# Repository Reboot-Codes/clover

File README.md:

<div align="center">

# C.L.O.V.E.R.

### Cybernetic Living Organism Variable Extension Regulator; Smart fursuit parts made for daily wear to help out your species dysphoria.

**Please note:** Clover is Currently NOT suitible for any sort of regular use and is being developed in sparse sprints as we can find time to do so.

</div>

---

## Features

- **Ease of Setup:** C.L.O.V.E.R.'s management software includes step by step guides on building, setup, and maintenence.
- **Focus on Security:** Every event and module is verified and authenticated with an explicit trust and permission framework *by the user*.
- **Open Extensibility:** C.L.O.V.E.R. ships with FLOSS APIs and an application management system which promotes open source projects.
- **Use Case Adaptability:** While originally designed for use in Smart Fursuits, C.L.O.V.E.R. can also be used for Cosplay and Body Modifications (e.g. Cyborgs).

## Usage

The currently planned workflow is to:

1. install a management application on an external device (like a PC, Laptop, Smartphone, or Tablet)
2. use it to plan out required materials, 
3. connect them, 
4. and flash them to create a working instance of C.L.O.V.E.R. 

Due to OS limitations, a linux/darwin desktop or a powerful android device is required for building C.L.O.V.E.R. firmwares. Otherwise, anything that supports the communication protocols configured in your instance and that has an application which speaks the management API can be used for external management/control once authenticated.

We also plan to make pre-built binaries available through a Nix cache to cut down on build times for CloverHub, C.O.R.E. components, and some supported configurations; but offline builds will always be an option.

## License, Disclaimer, and Other Legal Preface

C.L.O.V.E.R.'s primary orchestration process(es, a.k.a. CloverHub), reference API implementations (Tesseract, CarbonSteel, CarbonFiber), management software (Spanner), hardware (C.O.R.E.), and documentation are licensed under the GNU Affero General Public License version 3. CloverHub ships with or will download a copy of the repository it was built from to run C.O.R.E. and ensure AGPL compliance.

Software developed with any reference API implementations (Tesseract, CarbonSteel) may be covered under the AGPL as well. ***This is not legal advice***, but a notice to developers who may be considering building for C.L.O.V.E.R., that you may be required to publish your source code in accordance with the AGPL if you choose to make your software publicly accessable at all.

Of course, any contributor to this repository and associated materials does not provide any guarantee of any kind, nor will take liability for actions caused by or relating to C.L.O.V.E.R.

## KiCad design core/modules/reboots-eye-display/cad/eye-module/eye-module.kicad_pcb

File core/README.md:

# CORE

### C.L.O.V.E.R.'s Organizational Robotic Extremities; The offically maintained modules, applications, and expression packs for C.L.O.V.E.R.

[Check the docs for more info.](https://clover.reboot-codes.com/docs/core/intro)

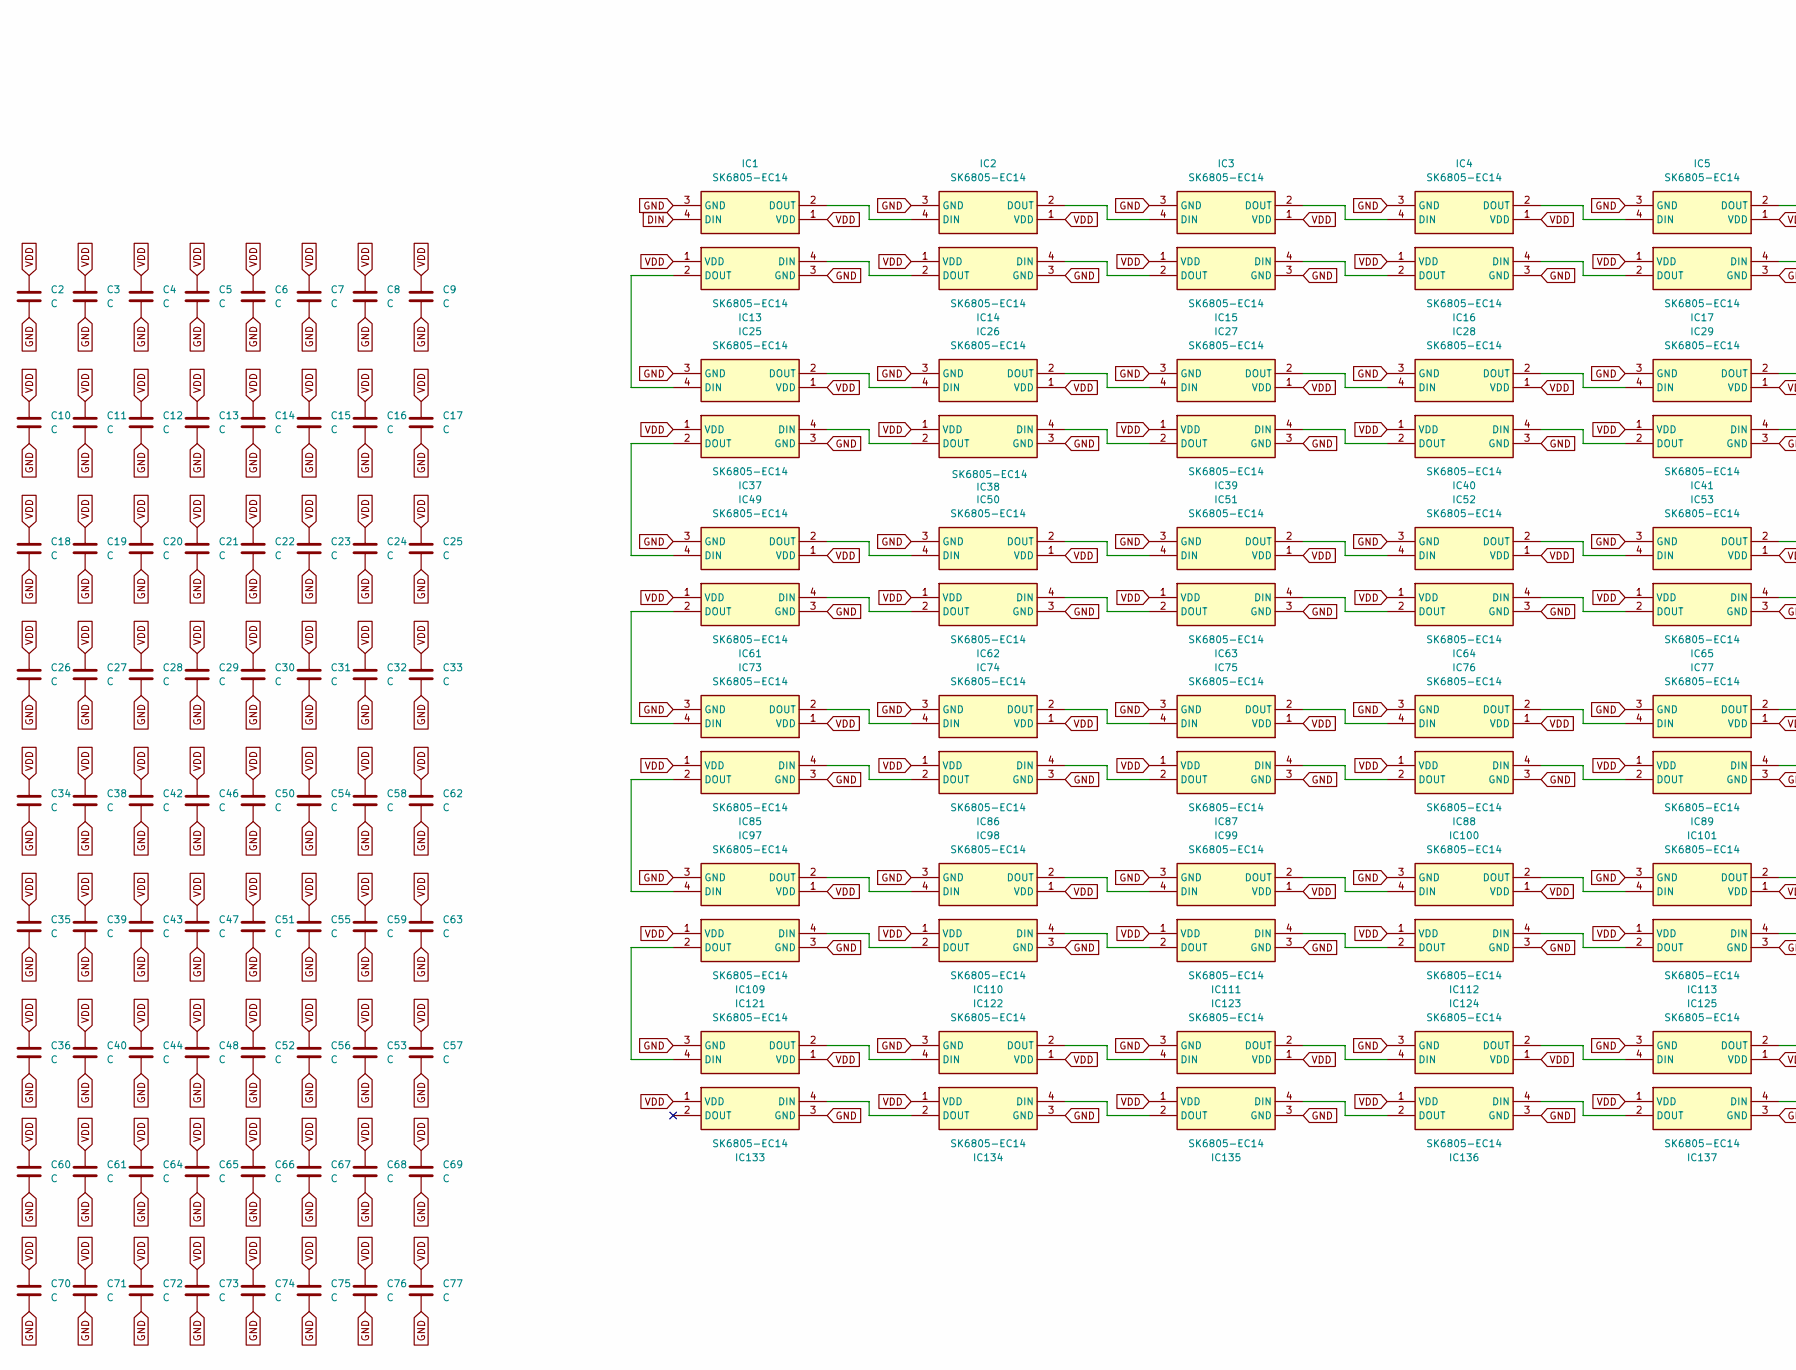
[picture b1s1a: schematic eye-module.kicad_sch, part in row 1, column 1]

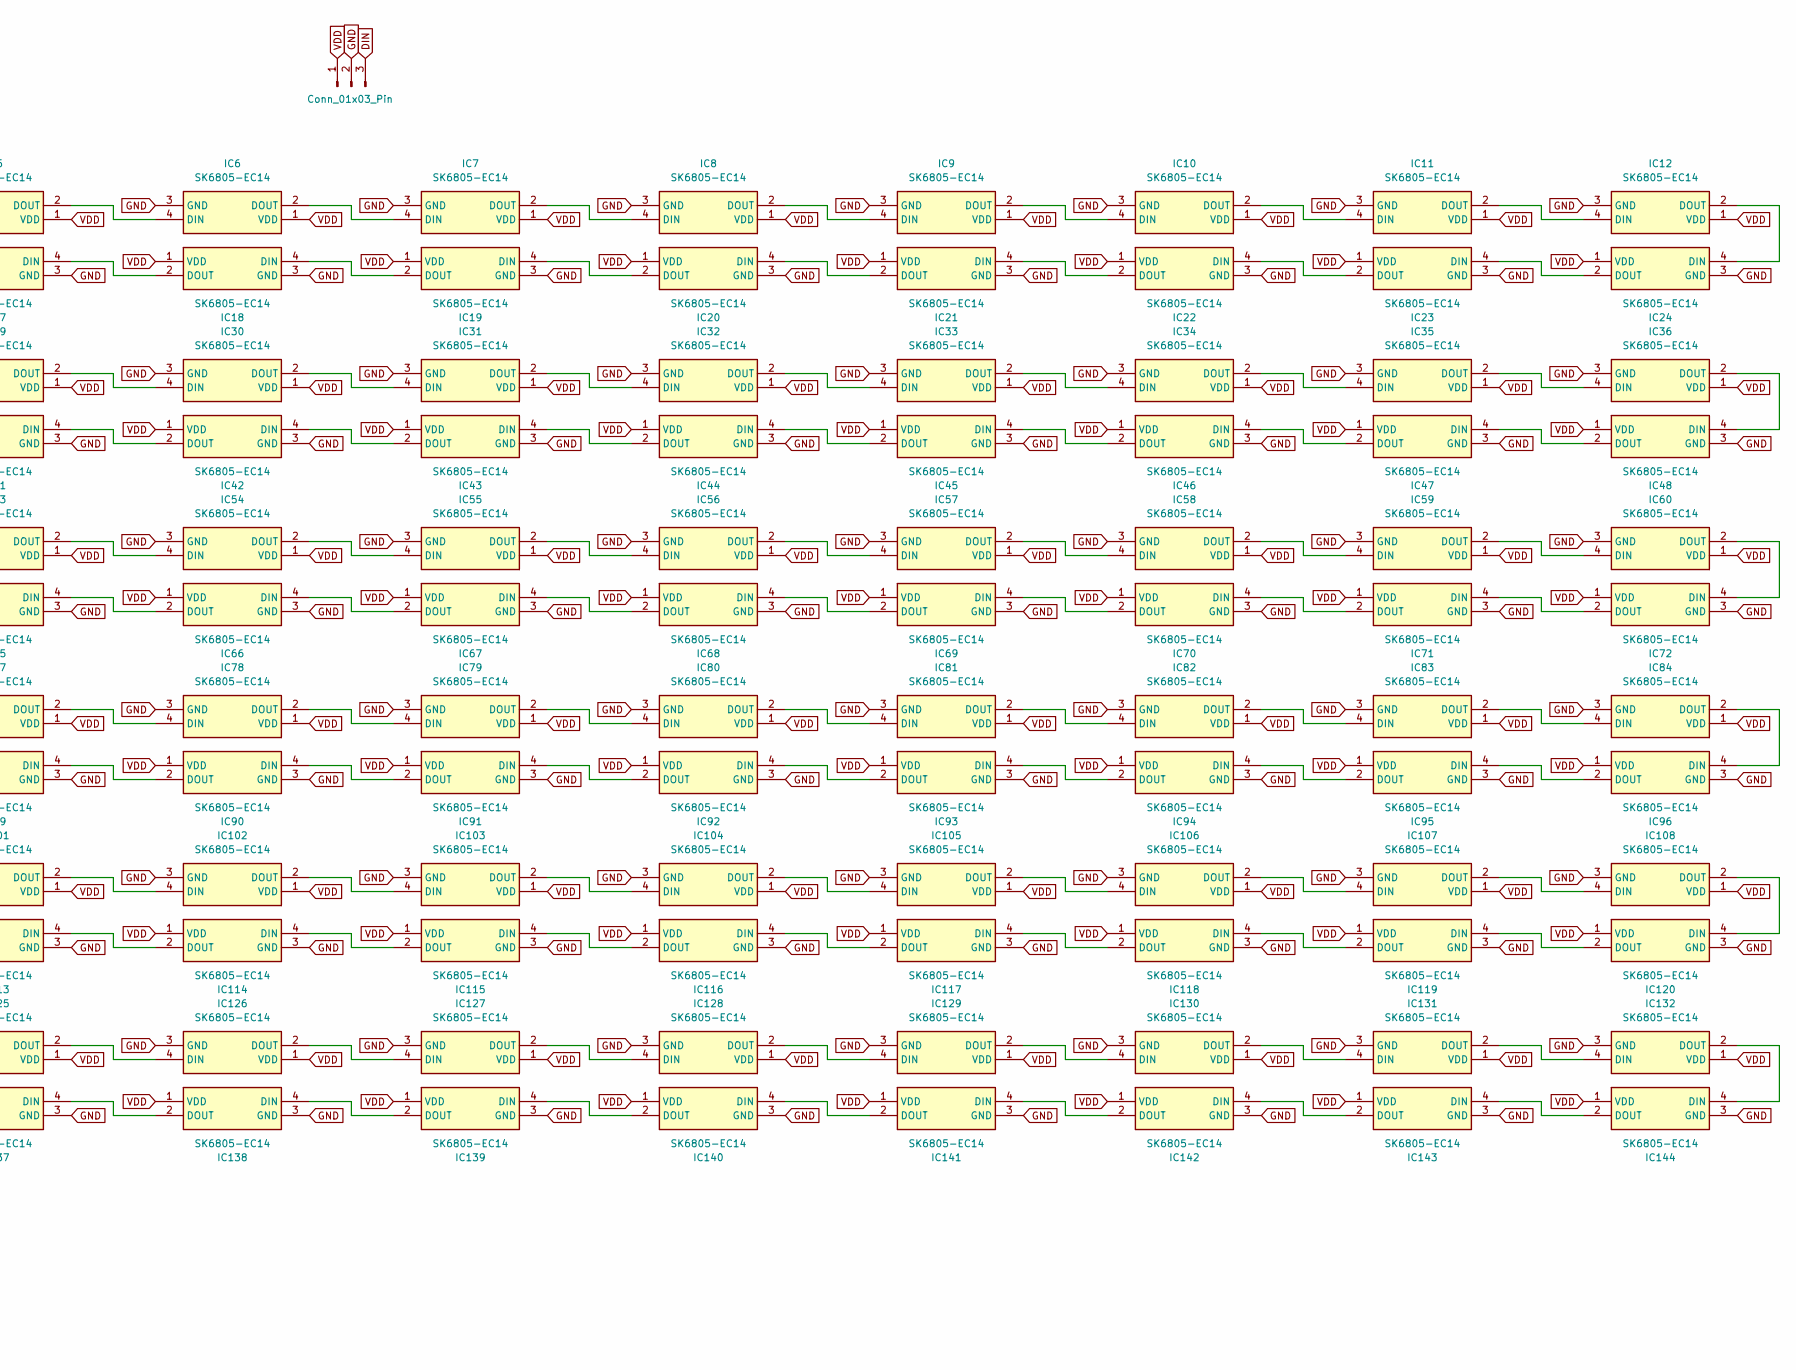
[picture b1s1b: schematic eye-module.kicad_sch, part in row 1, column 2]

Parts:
C2, C3, C4, C5, C6, C7, C8, C9, C10, C11, C12, C13, C14, C15, C16, C17, C18, C19, C20, C21, C22, C23, C24, C25, C26, C27, C28, C29, C30, C31, C32, C33, C34, C35, C36, C38, C39, C40, C42, C43, C44, C46, C47, C48, C50, C51, C52, C53, C54, C55, C56, C57, C58, C59, C60, C61, C62, C63, C64, C65, C66, C67, C68, C69, C70, C71, C72, C73, C74, C75, C76, C77: C; C_0603_1608Metric
IC1, IC2, IC3, IC4, IC5, IC6, IC7, IC8, IC9, IC10, IC11, IC12, IC13, IC14, IC15, IC16, IC17, IC18, IC19, IC20, IC21, IC22, IC23, IC24, IC25, IC26, IC27, IC28, IC29, IC30, IC31, IC32, IC33, IC34, IC35, IC36, IC37, IC38, IC39, IC40, IC41, IC42, IC43, IC44, IC45, IC46, IC47, IC48, IC49, IC50, IC51, IC52, IC53, IC54, IC55, IC56, IC57, IC58, IC59, IC60, IC61, IC62, IC63, IC64, IC65, IC66, IC67, IC68, IC69, IC70, IC71, IC72, IC73, IC74, IC75, IC76, IC77, IC78, IC79, IC80, IC81, IC82, IC83, IC84, IC85, IC86, IC87, IC88, IC89, IC90, IC91, IC92, IC93, IC94, IC95, IC96, IC97, IC98, IC99, IC100, IC101, IC102, IC103, IC104, IC105, IC106, IC107, IC108, IC109, IC110, IC111, IC112, IC113, IC114, IC115, IC116, IC117, IC118, IC119, IC120, IC121, IC122, IC123, IC124, IC125, IC126, IC127, IC128, IC129, IC130, IC131, IC132, IC133, IC134, IC135, IC136, IC137, IC138, IC139, IC140, IC141, IC142, IC143, IC144: SK6805-EC14; LED_SK6805_EC14; Manufacturer_Part_Number sk6805-ec14
J1: Conn_01x03_Pin; PinHeader_1x03_P1.00mm_Horizontal

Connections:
DIN: IC1.4 (DIN), J1.3
GND: C2.2, C3.2, C4.2, C5.2, C6.2, C7.2, C8.2, C9.2, C10.2, C11.2, C12.2, C13.2, C14.2, C15.2, C16.2, C17.2, C18.2, C19.2, C20.2, C21.2, C22.2, C23.2, C24.2, C25.2, C26.2, C27.2, C28.2, C29.2, C30.2, C31.2, C32.2, C33.2, C34.2, C35.2, C36.2, C38.2, C39.2, C40.2, C42.2, C43.2, C44.2, C46.2, C47.2, C48.2, C50.2, C51.2, C52.2, C53.2, C54.2, C55.2, C56.2, C57.2, C58.2, C59.2, C60.2, C61.2, C62.2, C63.2, C64.2, C65.2, C66.2, C67.2, C68.2, C69.2, C70.2, C71.2, C72.2, C73.2, C74.2, C75.2, C76.2, C77.2, IC1.3 (GND), IC2.3 (GND), IC3.3 (GND), IC4.3 (GND), IC5.3 (GND), IC6.3 (GND), IC7.3 (GND), IC8.3 (GND), IC9.3 (GND), IC10.3 (GND), IC11.3 (GND), IC12.3 (GND), IC13.3 (GND), IC14.3 (GND), IC15.3 (GND), IC16.3 (GND), IC17.3 (GND), IC18.3 (GND), IC19.3 (GND), IC20.3 (GND), IC21.3 (GND), IC22.3 (GND), IC23.3 (GND), IC24.3 (GND), IC25.3 (GND), IC26.3 (GND), IC27.3 (GND), IC28.3 (GND), IC29.3 (GND), IC30.3 (GND), IC31.3 (GND), IC32.3 (GND), IC33.3 (GND), IC34.3 (GND), IC35.3 (GND), IC36.3 (GND), IC37.3 (GND), IC38.3 (GND), IC39.3 (GND), IC40.3 (GND), IC41.3 (GND), IC42.3 (GND), IC43.3 (GND), IC44.3 (GND), IC45.3 (GND), IC46.3 (GND), IC47.3 (GND), IC48.3 (GND), IC49.3 (GND), IC50.3 (GND), IC51.3 (GND), IC52.3 (GND), IC53.3 (GND), IC54.3 (GND), IC55.3 (GND), IC56.3 (GND), IC57.3 (GND), IC58.3 (GND), IC59.3 (GND), IC60.3 (GND), IC61.3 (GND), IC62.3 (GND), IC63.3 (GND), IC64.3 (GND), IC65.3 (GND), IC66.3 (GND), IC67.3 (GND), IC68.3 (GND), IC69.3 (GND), IC70.3 (GND), IC71.3 (GND), IC72.3 (GND), IC73.3 (GND), IC74.3 (GND), IC75.3 (GND), IC76.3 (GND), IC77.3 (GND), IC78.3 (GND), IC79.3 (GND), IC80.3 (GND), IC81.3 (GND), IC82.3 (GND), IC83.3 (GND), IC84.3 (GND), IC85.3 (GND), IC86.3 (GND), IC87.3 (GND), IC88.3 (GND), IC89.3 (GND), IC90.3 (GND), IC91.3 (GND), IC92.3 (GND), IC93.3 (GND), IC94.3 (GND), IC95.3 (GND), IC96.3 (GND), IC97.3 (GND), IC98.3 (GND), IC99.3 (GND), IC100.3 (GND), IC101.3 (GND), IC102.3 (GND), IC103.3 (GND), IC104.3 (GND), IC105.3 (GND), IC106.3 (GND), IC107.3 (GND), IC108.3 (GND), IC109.3 (GND), IC110.3 (GND), IC111.3 (GND), IC112.3 (GND), IC113.3 (GND), IC114.3 (GND), IC115.3 (GND), IC116.3 (GND), IC117.3 (GND), IC118.3 (GND), IC119.3 (GND), IC120.3 (GND), IC121.3 (GND), IC122.3 (GND), IC123.3 (GND), IC124.3 (GND), IC125.3 (GND), IC126.3 (GND), IC127.3 (GND), IC128.3 (GND), IC129.3 (GND), IC130.3 (GND), IC131.3 (GND), IC132.3 (GND), IC133.3 (GND), IC134.3 (GND), IC135.3 (GND), IC136.3 (GND), IC137.3 (GND), IC138.3 (GND), IC139.3 (GND), IC140.3 (GND), IC141.3 (GND), IC142.3 (GND), IC143.3 (GND), IC144.3 (GND), J1.2
unnamed: IC1.2 (DOUT), IC2.4 (DIN)
unnamed: IC2.2 (DOUT), IC3.4 (DIN)
unnamed: IC3.2 (DOUT), IC4.4 (DIN)
unnamed: IC4.2 (DOUT), IC5.4 (DIN)
unnamed: IC5.2 (DOUT), IC6.4 (DIN)
unnamed: IC6.2 (DOUT), IC7.4 (DIN)
unnamed: IC7.2 (DOUT), IC8.4 (DIN)
unnamed: IC8.2 (DOUT), IC9.4 (DIN)
unnamed: IC9.2 (DOUT), IC10.4 (DIN)
unnamed: IC10.2 (DOUT), IC11.4 (DIN)
unnamed: IC11.2 (DOUT), IC12.4 (DIN)
unnamed: IC12.2 (DOUT), IC24.4 (DIN)
unnamed: IC13.4 (DIN), IC14.2 (DOUT)
unnamed: IC13.2 (DOUT), IC25.4 (DIN)
unnamed: IC14.4 (DIN), IC15.2 (DOUT)
unnamed: IC15.4 (DIN), IC16.2 (DOUT)
unnamed: IC16.4 (DIN), IC17.2 (DOUT)
unnamed: IC17.4 (DIN), IC18.2 (DOUT)
unnamed: IC18.4 (DIN), IC19.2 (DOUT)
unnamed: IC19.4 (DIN), IC20.2 (DOUT)
unnamed: IC20.4 (DIN), IC21.2 (DOUT)
unnamed: IC21.4 (DIN), IC22.2 (DOUT)
unnamed: IC22.4 (DIN), IC23.2 (DOUT)
unnamed: IC23.4 (DIN), IC24.2 (DOUT)
unnamed: IC25.2 (DOUT), IC26.4 (DIN)
unnamed: IC26.2 (DOUT), IC27.4 (DIN)
unnamed: IC27.2 (DOUT), IC28.4 (DIN)
unnamed: IC28.2 (DOUT), IC29.4 (DIN)
unnamed: IC29.2 (DOUT), IC30.4 (DIN)
unnamed: IC30.2 (DOUT), IC31.4 (DIN)
unnamed: IC31.2 (DOUT), IC32.4 (DIN)
unnamed: IC32.2 (DOUT), IC33.4 (DIN)
unnamed: IC33.2 (DOUT), IC34.4 (DIN)
unnamed: IC34.2 (DOUT), IC35.4 (DIN)
unnamed: IC35.2 (DOUT), IC36.4 (DIN)
unnamed: IC36.2 (DOUT), IC48.4 (DIN)
unnamed: IC37.4 (DIN), IC38.2 (DOUT)
unnamed: IC37.2 (DOUT), IC49.4 (DIN)
unnamed: IC38.4 (DIN), IC39.2 (DOUT)
unnamed: IC39.4 (DIN), IC40.2 (DOUT)
unnamed: IC40.4 (DIN), IC41.2 (DOUT)
unnamed: IC41.4 (DIN), IC42.2 (DOUT)
unnamed: IC42.4 (DIN), IC43.2 (DOUT)
unnamed: IC43.4 (DIN), IC44.2 (DOUT)
unnamed: IC44.4 (DIN), IC45.2 (DOUT)
unnamed: IC45.4 (DIN), IC46.2 (DOUT)
unnamed: IC46.4 (DIN), IC47.2 (DOUT)
unnamed: IC47.4 (DIN), IC48.2 (DOUT)
unnamed: IC49.2 (DOUT), IC50.4 (DIN)
unnamed: IC50.2 (DOUT), IC51.4 (DIN)
unnamed: IC51.2 (DOUT), IC52.4 (DIN)
unnamed: IC52.2 (DOUT), IC53.4 (DIN)
unnamed: IC53.2 (DOUT), IC54.4 (DIN)
unnamed: IC54.2 (DOUT), IC55.4 (DIN)
unnamed: IC55.2 (DOUT), IC56.4 (DIN)
unnamed: IC56.2 (DOUT), IC57.4 (DIN)
unnamed: IC57.2 (DOUT), IC58.4 (DIN)
unnamed: IC58.2 (DOUT), IC59.4 (DIN)
unnamed: IC59.2 (DOUT), IC60.4 (DIN)
unnamed: IC60.2 (DOUT), IC72.4 (DIN)
unnamed: IC61.4 (DIN), IC62.2 (DOUT)
unnamed: IC61.2 (DOUT), IC73.4 (DIN)
unnamed: IC62.4 (DIN), IC63.2 (DOUT)
unnamed: IC63.4 (DIN), IC64.2 (DOUT)
unnamed: IC64.4 (DIN), IC65.2 (DOUT)
unnamed: IC65.4 (DIN), IC66.2 (DOUT)
unnamed: IC66.4 (DIN), IC67.2 (DOUT)
unnamed: IC67.4 (DIN), IC68.2 (DOUT)
unnamed: IC68.4 (DIN), IC69.2 (DOUT)
unnamed: IC69.4 (DIN), IC70.2 (DOUT)
unnamed: IC70.4 (DIN), IC71.2 (DOUT)
unnamed: IC71.4 (DIN), IC72.2 (DOUT)
unnamed: IC73.2 (DOUT), IC74.4 (DIN)
unnamed: IC74.2 (DOUT), IC75.4 (DIN)
unnamed: IC75.2 (DOUT), IC76.4 (DIN)
unnamed: IC76.2 (DOUT), IC77.4 (DIN)
unnamed: IC77.2 (DOUT), IC78.4 (DIN)
unnamed: IC78.2 (DOUT), IC79.4 (DIN)
unnamed: IC79.2 (DOUT), IC80.4 (DIN)
unnamed: IC80.2 (DOUT), IC81.4 (DIN)
unnamed: IC81.2 (DOUT), IC82.4 (DIN)
unnamed: IC82.2 (DOUT), IC83.4 (DIN)
unnamed: IC83.2 (DOUT), IC84.4 (DIN)
unnamed: IC84.2 (DOUT), IC96.4 (DIN)
unnamed: IC85.4 (DIN), IC86.2 (DOUT)
unnamed: IC85.2 (DOUT), IC97.4 (DIN)
unnamed: IC86.4 (DIN), IC87.2 (DOUT)
unnamed: IC87.4 (DIN), IC88.2 (DOUT)
unnamed: IC88.4 (DIN), IC89.2 (DOUT)
unnamed: IC89.4 (DIN), IC90.2 (DOUT)
unnamed: IC90.4 (DIN), IC91.2 (DOUT)
unnamed: IC91.4 (DIN), IC92.2 (DOUT)
unnamed: IC92.4 (DIN), IC93.2 (DOUT)
unnamed: IC93.4 (DIN), IC94.2 (DOUT)
unnamed: IC94.4 (DIN), IC95.2 (DOUT)
unnamed: IC95.4 (DIN), IC96.2 (DOUT)
unnamed: IC97.2 (DOUT), IC98.4 (DIN)
unnamed: IC98.2 (DOUT), IC99.4 (DIN)
unnamed: IC99.2 (DOUT), IC100.4 (DIN)
unnamed: IC100.2 (DOUT), IC101.4 (DIN)
unnamed: IC101.2 (DOUT), IC102.4 (DIN)
unnamed: IC102.2 (DOUT), IC103.4 (DIN)
unnamed: IC103.2 (DOUT), IC104.4 (DIN)
unnamed: IC104.2 (DOUT), IC105.4 (DIN)
unnamed: IC105.2 (DOUT), IC106.4 (DIN)
unnamed: IC106.2 (DOUT), IC107.4 (DIN)
unnamed: IC107.2 (DOUT), IC108.4 (DIN)
unnamed: IC108.2 (DOUT), IC120.4 (DIN)
unnamed: IC109.4 (DIN), IC110.2 (DOUT)
unnamed: IC109.2 (DOUT), IC121.4 (DIN)
unnamed: IC110.4 (DIN), IC111.2 (DOUT)
unnamed: IC111.4 (DIN), IC112.2 (DOUT)
unnamed: IC112.4 (DIN), IC113.2 (DOUT)
unnamed: IC113.4 (DIN), IC114.2 (DOUT)
unnamed: IC114.4 (DIN), IC115.2 (DOUT)
unnamed: IC115.4 (DIN), IC116.2 (DOUT)
unnamed: IC116.4 (DIN), IC117.2 (DOUT)
unnamed: IC117.4 (DIN), IC118.2 (DOUT)
unnamed: IC118.4 (DIN), IC119.2 (DOUT)
unnamed: IC119.4 (DIN), IC120.2 (DOUT)
unnamed: IC121.2 (DOUT), IC122.4 (DIN)
unnamed: IC122.2 (DOUT), IC123.4 (DIN)
unnamed: IC123.2 (DOUT), IC124.4 (DIN)
unnamed: IC124.2 (DOUT), IC125.4 (DIN)
unnamed: IC125.2 (DOUT), IC126.4 (DIN)
unnamed: IC126.2 (DOUT), IC127.4 (DIN)
unnamed: IC127.2 (DOUT), IC128.4 (DIN)
unnamed: IC128.2 (DOUT), IC129.4 (DIN)
unnamed: IC129.2 (DOUT), IC130.4 (DIN)
unnamed: IC130.2 (DOUT), IC131.4 (DIN)
unnamed: IC131.2 (DOUT), IC132.4 (DIN)
unnamed: IC132.2 (DOUT), IC144.4 (DIN)
unnamed: IC133.4 (DIN), IC134.2 (DOUT)
unnamed: IC134.4 (DIN), IC135.2 (DOUT)
unnamed: IC135.4 (DIN), IC136.2 (DOUT)
unnamed: IC136.4 (DIN), IC137.2 (DOUT)
unnamed: IC137.4 (DIN), IC138.2 (DOUT)
unnamed: IC138.4 (DIN), IC139.2 (DOUT)
unnamed: IC139.4 (DIN), IC140.2 (DOUT)
unnamed: IC140.4 (DIN), IC141.2 (DOUT)
unnamed: IC141.4 (DIN), IC142.2 (DOUT)
unnamed: IC142.4 (DIN), IC143.2 (DOUT)
unnamed: IC143.4 (DIN), IC144.2 (DOUT)
VDD: C2.1, C3.1, C4.1, C5.1, C6.1, C7.1, C8.1, C9.1, C10.1, C11.1, C12.1, C13.1, C14.1, C15.1, C16.1, C17.1, C18.1, C19.1, C20.1, C21.1, C22.1, C23.1, C24.1, C25.1, C26.1, C27.1, C28.1, C29.1, C30.1, C31.1, C32.1, C33.1, C34.1, C35.1, C36.1, C38.1, C39.1, C40.1, C42.1, C43.1, C44.1, C46.1, C47.1, C48.1, C50.1, C51.1, C52.1, C53.1, C54.1, C55.1, C56.1, C57.1, C58.1, C59.1, C60.1, C61.1, C62.1, C63.1, C64.1, C65.1, C66.1, C67.1, C68.1, C69.1, C70.1, C71.1, C72.1, C73.1, C74.1, C75.1, C76.1, C77.1, IC1.1 (VDD), IC2.1 (VDD), IC3.1 (VDD), IC4.1 (VDD), IC5.1 (VDD), IC6.1 (VDD), IC7.1 (VDD), IC8.1 (VDD), IC9.1 (VDD), IC10.1 (VDD), IC11.1 (VDD), IC12.1 (VDD), IC13.1 (VDD), IC14.1 (VDD), IC15.1 (VDD), IC16.1 (VDD), IC17.1 (VDD), IC18.1 (VDD), IC19.1 (VDD), IC20.1 (VDD), IC21.1 (VDD), IC22.1 (VDD), IC23.1 (VDD), IC24.1 (VDD), IC25.1 (VDD), IC26.1 (VDD), IC27.1 (VDD), IC28.1 (VDD), IC29.1 (VDD), IC30.1 (VDD), IC31.1 (VDD), IC32.1 (VDD), IC33.1 (VDD), IC34.1 (VDD), IC35.1 (VDD), IC36.1 (VDD), IC37.1 (VDD), IC38.1 (VDD), IC39.1 (VDD), IC40.1 (VDD), IC41.1 (VDD), IC42.1 (VDD), IC43.1 (VDD), IC44.1 (VDD), IC45.1 (VDD), IC46.1 (VDD), IC47.1 (VDD), IC48.1 (VDD), IC49.1 (VDD), IC50.1 (VDD), IC51.1 (VDD), IC52.1 (VDD), IC53.1 (VDD), IC54.1 (VDD), IC55.1 (VDD), IC56.1 (VDD), IC57.1 (VDD), IC58.1 (VDD), IC59.1 (VDD), IC60.1 (VDD), IC61.1 (VDD), IC62.1 (VDD), IC63.1 (VDD), IC64.1 (VDD), IC65.1 (VDD), IC66.1 (VDD), IC67.1 (VDD), IC68.1 (VDD), IC69.1 (VDD), IC70.1 (VDD), IC71.1 (VDD), IC72.1 (VDD), IC73.1 (VDD), IC74.1 (VDD), IC75.1 (VDD), IC76.1 (VDD), IC77.1 (VDD), IC78.1 (VDD), IC79.1 (VDD), IC80.1 (VDD), IC81.1 (VDD), IC82.1 (VDD), IC83.1 (VDD), IC84.1 (VDD), IC85.1 (VDD), IC86.1 (VDD), IC87.1 (VDD), IC88.1 (VDD), IC89.1 (VDD), IC90.1 (VDD), IC91.1 (VDD), IC92.1 (VDD), IC93.1 (VDD), IC94.1 (VDD), IC95.1 (VDD), IC96.1 (VDD), IC97.1 (VDD), IC98.1 (VDD), IC99.1 (VDD), IC100.1 (VDD), IC101.1 (VDD), IC102.1 (VDD), IC103.1 (VDD), IC104.1 (VDD), IC105.1 (VDD), IC106.1 (VDD), IC107.1 (VDD), IC108.1 (VDD), IC109.1 (VDD), IC110.1 (VDD), IC111.1 (VDD), IC112.1 (VDD), IC113.1 (VDD), IC114.1 (VDD), IC115.1 (VDD), IC116.1 (VDD), IC117.1 (VDD), IC118.1 (VDD), IC119.1 (VDD), IC120.1 (VDD), IC121.1 (VDD), IC122.1 (VDD), IC123.1 (VDD), IC124.1 (VDD), IC125.1 (VDD), IC126.1 (VDD), IC127.1 (VDD), IC128.1 (VDD), IC129.1 (VDD), IC130.1 (VDD), IC131.1 (VDD), IC132.1 (VDD), IC133.1 (VDD), IC134.1 (VDD), IC135.1 (VDD), IC136.1 (VDD), IC137.1 (VDD), IC138.1 (VDD), IC139.1 (VDD), IC140.1 (VDD), IC141.1 (VDD), IC142.1 (VDD), IC143.1 (VDD), IC144.1 (VDD), J1.1

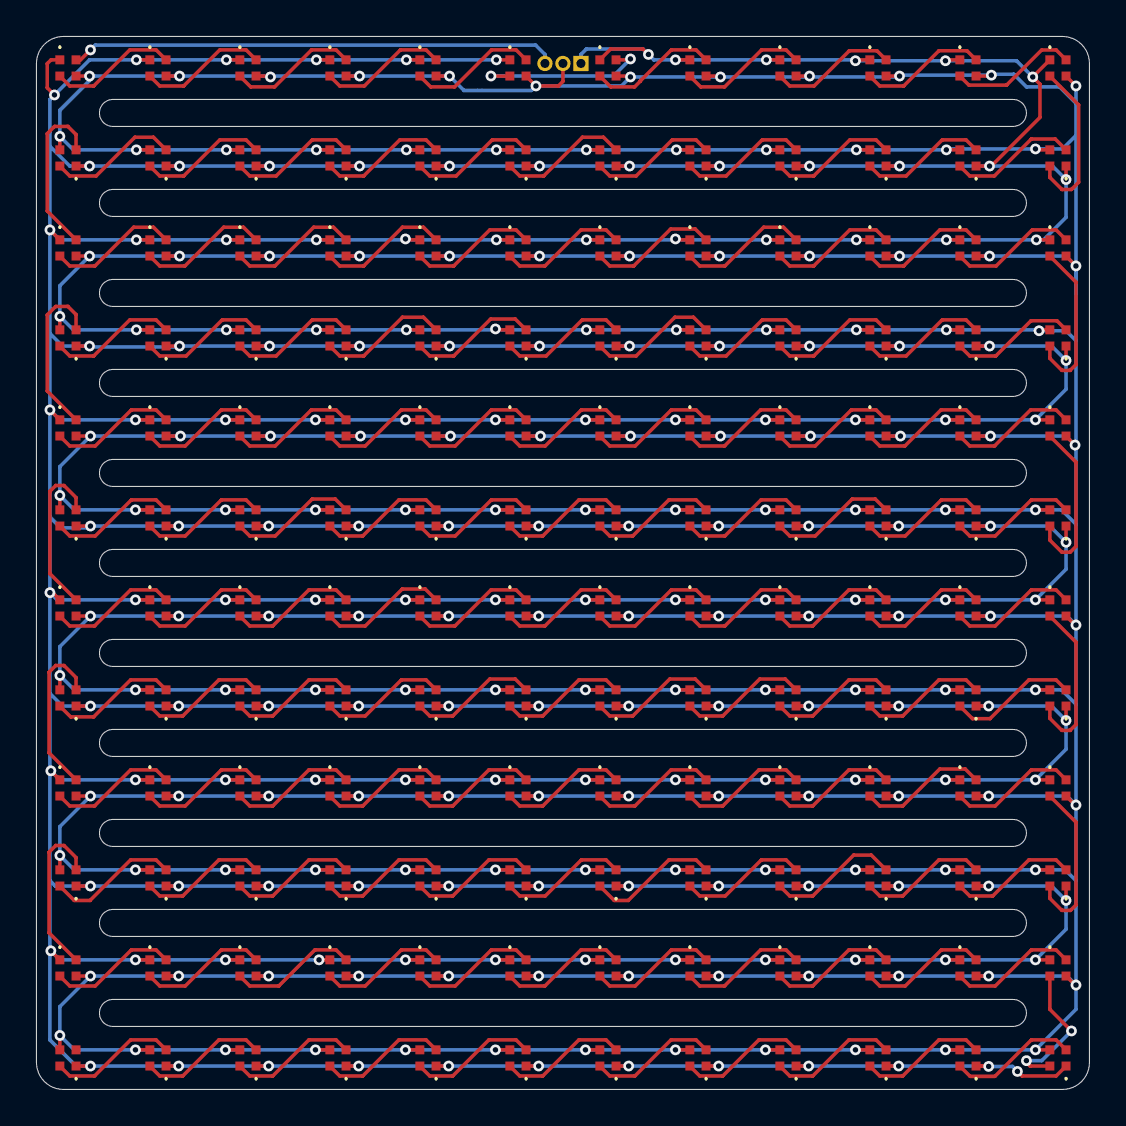
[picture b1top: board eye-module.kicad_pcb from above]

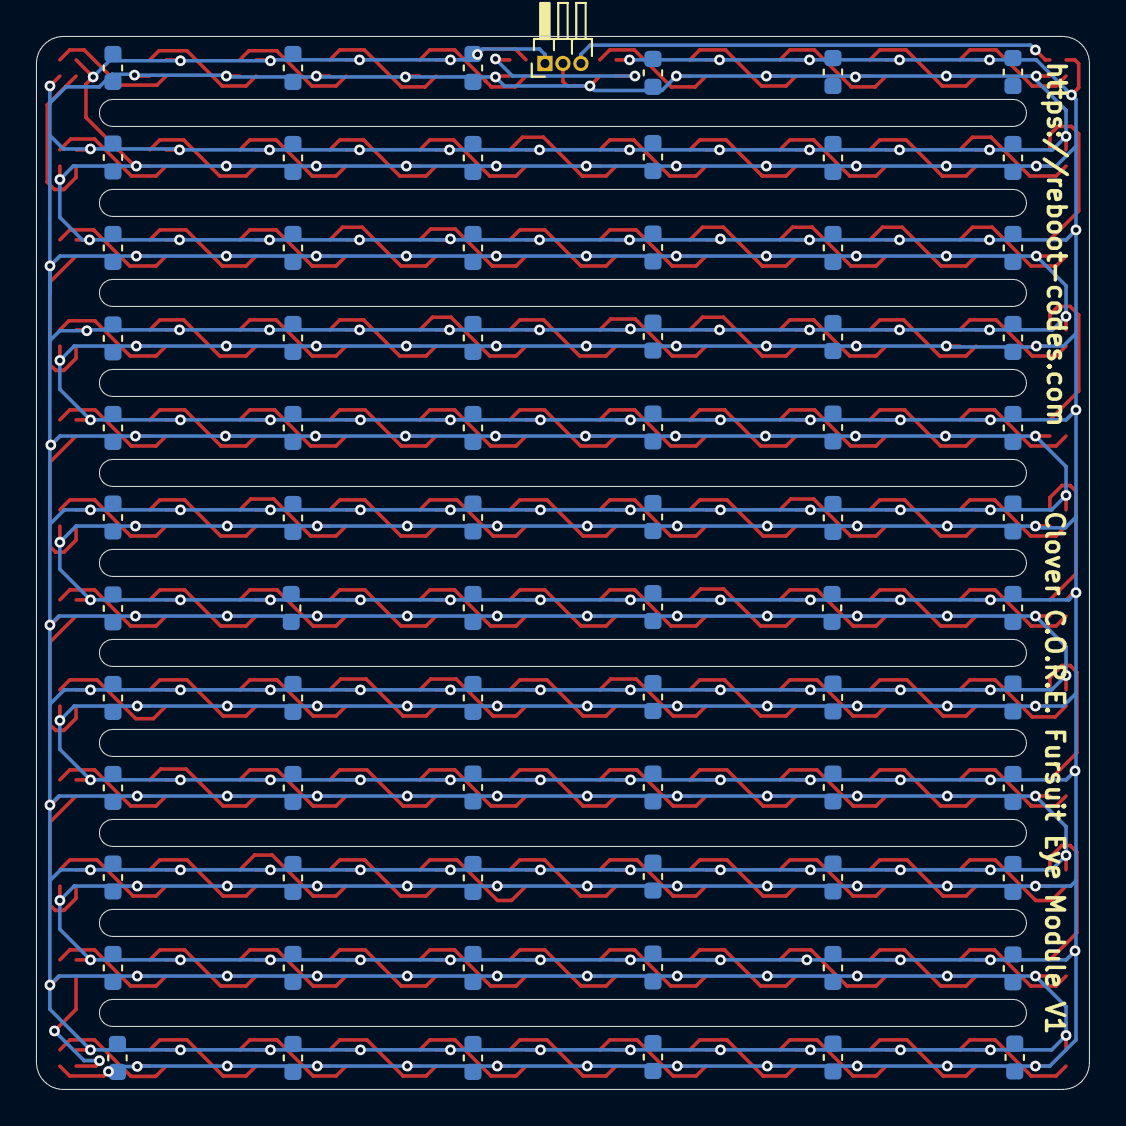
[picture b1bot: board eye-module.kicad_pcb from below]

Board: 2 copper layers, 58.5 x 58.5 mm, 217 parts (73 on the bottom side), 146 nets.

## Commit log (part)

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2024-08-06 Add message ids.
2024-08-06 Make sure to log the client that caused a WS error.
2024-08-06 Add docs website!
2024-08-06 Add the real readme...
2024-08-06 Add GH pages action.
2024-08-06 Fix node.js setup for GH Action.
2024-08-06 Shhhhhh~ I'm sure frozen lockfile doesn't matter for docs.
2024-08-06 Fix baseUrl and make sure docs builds only happen when docs are changed.
2024-08-07 Add `echo` option to API keys and add more docs.
2024-09-01 Reorganize server.
2024-09-01 Rename server to EVTBuzz
2024-09-01 Update docs to reflect new organization.
2024-09-01 Move to custom subdomain
2024-09-01 Fix broken docs links
2024-09-25 Add more IPC channels, add core user account generation.
2024-09-26 Complete IPC between core threads.
2024-09-26 Setup EvtBuzz's IPC dispatchers.
2024-09-27 Add Spanner to docs.
2024-09-27 Add deps on Taurus
2024-09-27 Refactor Models and Ensure Proper Formatting.
2024-09-27 Broken: Attempting SIGINT Handling, ModMan formation.
2024-09-28 Add stopping code. One module will always linger...?
2024-09-28 Fix SIGINT handling
2024-09-28 Add signal handling to all configs and add windows support.
2024-09-30 Move cargo config to root.
2024-09-30 Add spanner's template code and use cargo workspace.
2024-09-30 Restructure documentation.
2024-09-30 Fix broken links
2024-09-30 Clean up.
2024-09-30 Oops. Yeah, that's not the name of the executable anymore...
2024-09-30 Fix root domain
2024-10-01 Note to self: Move init hooks into cancelable closures.
2024-10-01 Remove the todo lol.
2024-10-01 Fix evtbuzz.
2024-10-02 Add more docs.
2024-10-03 Add more docs
2024-11-14 Add AppDaemon and Warehouse beginnings. Yeah, we need to stick to one thing at a time lmfao.
2024-11-14 Warehouse now manages configuration files properly.
2024-11-14 Add repository serialization
2024-11-14 Add libgit2 code to clone and update repos - todo: Create repo directory structure!
2024-11-15 Repo manifest resolution
2024-11-16 Module imports done... now for apps...
2024-11-17 More manifest import work (still broken)
2024-11-18 Majorly refactor repo manifest code - TL;DR: Using features built into the language you're using kinda makes things easier, ya kno?
2024-11-18 Start moving to async fs because it's hanging...
2024-11-19 Bump http-proxy-middleware from 2.0.6 to 2.0.7 in /docs
    Bumps [http-proxy-middleware](https://github.com/chimurai/http-proxy-middleware) from 2.0.6 to 2.0.7.
    - [Release notes](https://github.com/chimurai/http-proxy-middleware/releases)
    - [Changelog](https://github.com/chimurai/http-proxy-middleware/blob/v2.0.7/CHANGELOG.md)
    - [Commits](https://github.com/chimurai/http-proxy-middleware/compare/v2.0.6...v2.0.7)
    ---
    updated-dependencies:
2024-11-19 Fix repo import code (it compiles now!)
2024-11-19 More manifest format testing
2024-11-19 Works now?
2024-11-19 please...
2024-11-20 FUCK YOU
2024-11-21 YES imports work. Todo: fix key directives.
2024-11-22 ITS FIXED
2024-11-22 Add builtin intent.
2024-11-22 Actually... resolve directives in intents
2024-11-22 Make manifests more extension friendly and update documentation.
2024-11-22 Fix models.
2024-11-22 Very silly mistake...
2024-11-22 Fix core manifest. Update todo.md.
2024-11-22 Regulate graceful shutdown properly.
2024-11-22 Add the db.
2024-11-24 FUCK YEAHHHHHH
2024-11-24 Move to sea orm and sqlite. Make warehouse into an internal service.
2024-11-24 Add wgpu for `renderer`.
2024-11-25 Begin shader work.
2024-11-25 FIRST TRIANGLE
2024-11-26 I hate grapigixhdsz
2024-11-27 Move to QT, use Bevy for AppKit
2024-11-27 Move SystemUI to separate module.
2024-11-27 Faster builds using `mold`, compiler optimizations, and shared generics.
2024-11-27 Actually render things!!
2024-11-27 Fix input for testing.
2024-11-27 Bleh. Rename things.
2024-12-01 Move to deno and add packages for module bus proxies.
2024-12-04 Refactor SystemUI to make better use of compilation features.
2024-12-26 Fix shell env.
2024-12-26 Bump http-proxy-middleware from 2.0.6 to 2.0.7 in /docs (#1)
    Bumps [http-proxy-middleware](https://github.com/chimurai/http-proxy-middleware) from 2.0.6 to 2.0.7.
    - [Release notes](https://github.com/chimurai/http-proxy-middleware/releases)
    - [Changelog](https://github.com/chimurai/http-proxy-middleware/blob/v2.0.7/CHANGELOG.md)
    - [Commits](https://github.com/chimurai/http-proxy-middleware/compare/v2.0.6...v2.0.7)
    ---
    updated-dependencies:
2024-12-26 Bump nanoid from 3.3.7 to 3.3.8 in /docs
    Bumps [nanoid](https://github.com/ai/nanoid) from 3.3.7 to 3.3.8.
    - [Release notes](https://github.com/ai/nanoid/releases)
    - [Changelog](https://github.com/ai/nanoid/blob/main/CHANGELOG.md)
    - [Commits](https://github.com/ai/nanoid/compare/3.3.7...3.3.8)
    ---
    updated-dependencies:
2024-12-26 Bump nanoid from 3.3.7 to 3.3.8 in /docs (#2)
    Bumps [nanoid](https://github.com/ai/nanoid) from 3.3.7 to 3.3.8.
    - [Release notes](https://github.com/ai/nanoid/releases)
    - [Changelog](https://github.com/ai/nanoid/blob/main/CHANGELOG.md)
    - [Commits](https://github.com/ai/nanoid/compare/3.3.7...3.3.8)
    ---
    updated-dependencies:
2024-12-26 Bump cross-spawn from 7.0.3 to 7.0.6 in /docs
    Bumps [cross-spawn](https://github.com/moxystudio/node-cross-spawn) from 7.0.3 to 7.0.6.
    - [Changelog](https://github.com/moxystudio/node-cross-spawn/blob/master/CHANGELOG.md)
    - [Commits](https://github.com/moxystudio/node-cross-spawn/compare/v7.0.3...v7.0.6)
    ---
    updated-dependencies:
    - dependency-name: cross-spawn
2024-12-26 Bump cross-spawn from 7.0.3 to 7.0.6 in /docs (#3)
    Bumps [cross-spawn](https://github.com/moxystudio/node-cross-spawn) from 7.0.3 to 7.0.6.
    - [Changelog](https://github.com/moxystudio/node-cross-spawn/blob/master/CHANGELOG.md)
    - [Commits](https://github.com/moxystudio/node-cross-spawn/compare/v7.0.3...v7.0.6)
    ---
    updated-dependencies:
    - dependency-name: cross-spawn
2024-12-26 More android config.
2024-12-26 Bleh, versions
2024-12-29 Update docs with SystemUI work!
2024-12-29 Trying to fix formatting.
2025-01-05 Fix dependabot issue #17: Mio's tokens for named pipes may be delivered after deregistration
2025-01-05 Fix dependabot issue #25: Unpatched `path-to-regexp` ReDoS in 0.1.x
2025-03-11 SystemUI's built-in view management.
    - TODO: Do documentation for views.
2025-03-11 Fix dev env????
2025-03-12 Toolchain flake
2025-03-14 Formatting and properzed support :P
2025-03-15 Component specs...
2025-03-15 Component initalization prep!
2025-03-15 Lmfao, I forgor about custom name support... shit I need to add that to modules now too...
2025-03-15 Make sure it... runs lmfao. Everything's goin' good tho!
2025-03-19 Move evtbuzz to nexus
2025-04-04 It builds with nexus now!
2025-04-25 Fixed up event handling
2025-04-25 Fixing silly things with base64 parsing
2025-04-30 Add better gesture pack config support to components and begin area/acl controls.
2025-05-01 Setup sqlite and begin gesture ACL logic
2025-05-01 Refactor manifest files to use "gesture" instead of "expression"
2025-05-01 Damn. Trailing. Commas pt2 (moving to serde_json_lenient)
2025-05-01 Damn. Trailing. Commas pt3 (moving to serde_json_lenient)
2025-05-01 Damn. Trailing. Commas pt4 (moving to serde_json_lenient)
2025-05-01 That's my fault, whups
2025-05-01 Init function...
2025-05-01 Refactoring again
2025-05-01 Add de-init logic for modules
2025-05-03 Cleanup some hanging chads or whatever
2025-05-05 Start modman proxies. UART in testing stage!
2025-05-06 UART security pt 1
2025-05-09 Doing some hot BS with ALSA
2025-05-09 Try fixing up docs and move back to tauri because fuck qml actually
2025-05-09 Fix workflow?
2025-05-15 Restructure
2025-05-15 Restructure pt 2
2025-05-15 Oh. I had a git repo in a git repo. duh
2025-05-15 Oh. lol. I don't have eyes
2025-05-15 Use yarn berry?
2025-05-19 Starting ratchet...
2025-06-03 Move to Iced because nextjs sucks actually
2025-06-03 Add screen switching
2025-06-03 Formatting and such
2025-06-03 Add wizard step switching
2025-06-03 Spacing
2025-06-03 Add menu bar
2025-06-03 Menubar size betterment
2025-06-03 Styling
2025-06-04 Add repo detail screen
2025-06-06 Refactoring and allow for repo specific configuration w/o instance attached
2025-06-06 Add proper repo configuration focus
2025-07-07 Almost done with ratchet scaffolding
2025-07-09 FUCK YEAHHHH IT WORKS
2025-07-14 Relative dependancy on nexus
2025-08-17 Support statically configured virtual displays
2025-08-17 Make sure that bevy exits when clover-hub gets a sigint
2025-08-17 Make simulated controls interactive
2025-11-08 I forgot what I changed.
2026-02-01 Fix VK errors, Nexus init race condition, IPC Recv race condition, added UART config warning.
2026-02-02 Move to macro for generating repo manifest resolution code.
2026-02-25 Actually pin the toolchain, thx. Also cleanup!
2026-02-25 Fix dependabot issues.
2026-02-25 Gonna move ratchet to gpui anyways so whatever.
2026-05-19 Add AGPL license, update README.md to be nicer.
2026-05-21 Move CloverHub docs to RustDoc to ensure they get updated as clover gets developed.
2026-05-21 Start to move to Astro.
2026-05-22 Setup process-compose and begin moving to zenoh.
2026-05-22 Get rid of the shutdown callback pyramid.
2026-05-22 Start to use spans for tasks.
2026-05-22 Add OpenTelemetry to be used later with Tesseract and error reports.
2026-05-23 Fix rand sec-issue, start the move to zenoh.
2026-05-23 Initalize Flutter toolchain.
2026-05-24 Scaffold out Spanner properly.
2026-05-24 Get ready to use custom window controls.
2026-06-01 Actually work on the TUI.
2026-06-01 More moving to Astro
2026-06-16 Basic Zenoh ground work.
2026-06-17 Finish Zenoh boilerplating. Start moving real IPC to zenoh.
    Still need to move proxy busses to zenoh! Currently, there's a race
    condition between modman and renderer. Modman is currently hanging on
    module init due to a mutex await.
2026-06-17 Finish moving display query to zenoh.
2026-06-19 Remove Nexus completely, Fix Nix builds.
2026-06-20 Update connection logic, update UART bus to continous scanning.
    - Proxied connections should be global to the module, and not
    per-component.
    - Every bus proxy should also continously scan for requested bindings
    due to the dynamic nature of App Modules.
2026-06-20 chore: remove symlinks.
2026-06-20 chore: remove testing image artifact.
2026-06-20 chore: fix .gitignore... again.
    so many CI minutes being used on random crap lol. if I had CI that is.
